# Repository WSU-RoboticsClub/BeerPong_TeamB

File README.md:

# BeerPong Team B

This repository contains the microcontroller and PC code for Team B's beer-pong playing robot.

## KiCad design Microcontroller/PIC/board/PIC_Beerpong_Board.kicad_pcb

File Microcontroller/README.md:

Microcontroller
===============

This Folder Contains the Microcontroller Code for the Robot

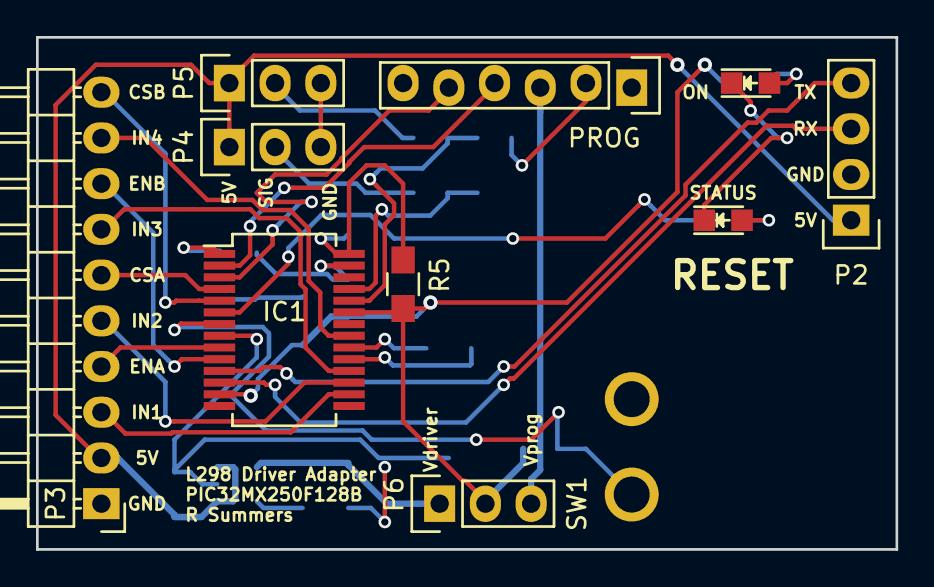
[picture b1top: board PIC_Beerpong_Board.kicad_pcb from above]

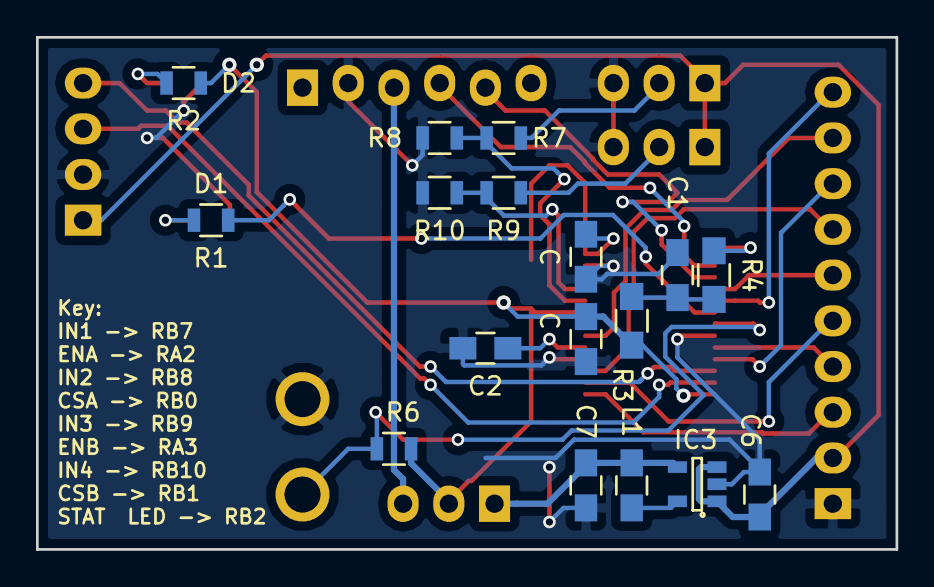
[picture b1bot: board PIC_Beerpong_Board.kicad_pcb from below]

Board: 2 copper layers, 47.8 x 28.4 mm, 28 parts (17 on the bottom side), 30 nets.

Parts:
C, C1, C2: C; C_0805_HandSoldering
C6: 4.7uF; C_0805_HandSoldering
C7: 10uF; C_0805_HandSoldering
C#2: C; C_0805_HandSoldering
D1, D2: LED; LED_0805
IC1: PIC32MX2xx/1xx; SSOP-28_5.3x10.2mm_Pitch0.65mm
IC3: LM3671; SOT-23-5
L1: 2.2uH; C_0805_HandSoldering
P2: CONN_01X04; Pin_Header_Straight_1x04
P3: CONN_01X10; Pin_Header_Angled_1x10
P4, P5, P6: CONN_01X03; Pin_Header_Straight_1x03
PROG: CONN_01X06; Pin_Header_Staggered_1x06
R1, R2, R6, R7, R8, R9, R10: R; R_0805
R3: 10k; R_0805_HandSoldering
R4: 470; R_0805_HandSoldering
R5: R; R_0805_HandSoldering
SW1: SW_PUSH; Switch

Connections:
+3V3: C.1, IC1.13, IC1.23, P6.2, R2.1, R3.1, R5.2, R6.1
+5V: C6.1, IC3.1, IC3.3, P2.1, P3.2, P4.1, P5.1
/3V3_PROG: P6.3, PROG.3
/HE1: P4.2, R9.1
/HE2: P5.2, R7.1
/Sheet56A51C6D/AVDD: C#2.1, IC1.28, R5.1
/Sheet56A51C6D/MRX: IC1.12, P2.3
/Sheet56A51C6D/MTX: IC1.11, P2.4
/Sheet56A51C6D/RA0: IC1.2, PROG.4
/Sheet56A51C6D/RA1: IC1.3, PROG.5
/Sheet56A51C6D/RA2: IC1.9, P3.4
/Sheet56A51C6D/RA3: IC1.10, P3.8
/Sheet56A51C6D/RB0: IC1.4, P3.6
/Sheet56A51C6D/RB1: IC1.5, P3.10
/Sheet56A51C6D/RB2: IC1.6, R1.1
/Sheet56A51C6D/RB3: IC1.7, R6.2, SW1.1
/Sheet56A51C6D/RB7: IC1.16, P3.3
/Sheet56A51C6D/RB8: IC1.17, P3.5
/Sheet56A51C6D/RB9: IC1.18, P3.7
/Sheet56A51C6D/RB10: IC1.21, P3.9
/Sheet56A51C6D/RB13: IC1.24, R7.2, R8.1
/Sheet56A51C6D/RB14: IC1.25, R9.2, R10.1
/Sheet56A51C6D/~MCLR: IC1.1, R4.1
/Sheet56A51CCD/Vout: C7.1, IC3.4, L1.2, P6.1
GND: C.2, C1.2, C2.2, C6.2, C7.2, C#2.2, D1.1, D2.1, IC1.8, IC1.19, IC1.27, IC3.2, P2.2, P3.1, P4.3, P5.3, PROG.2, R8.2, R10.2, SW1.2
unnamed: C1.1, R3.2, R4.2
unnamed: C2.1, IC1.20
unnamed: D1.2, R1.2
unnamed: D2.2, R2.2
unnamed: IC3.5, L1.1

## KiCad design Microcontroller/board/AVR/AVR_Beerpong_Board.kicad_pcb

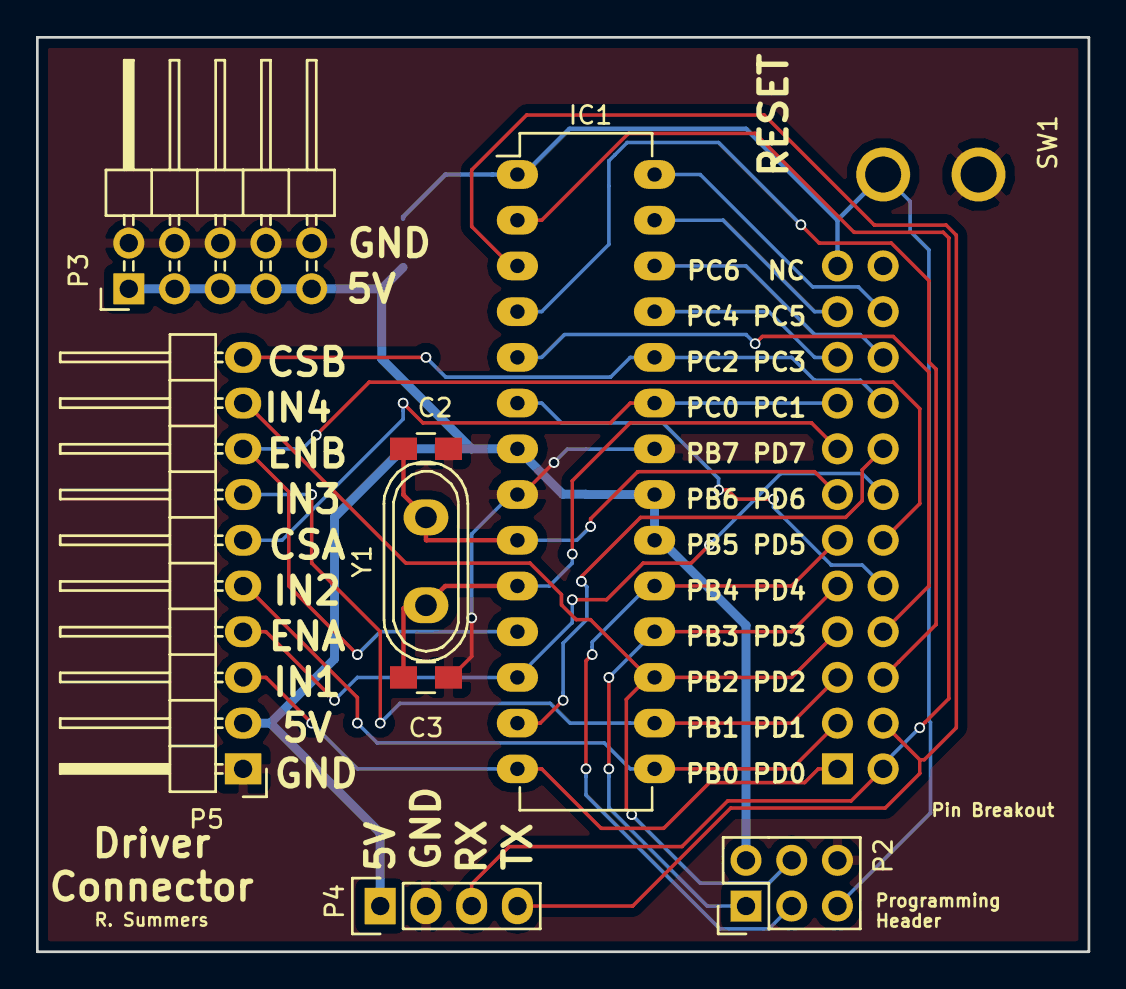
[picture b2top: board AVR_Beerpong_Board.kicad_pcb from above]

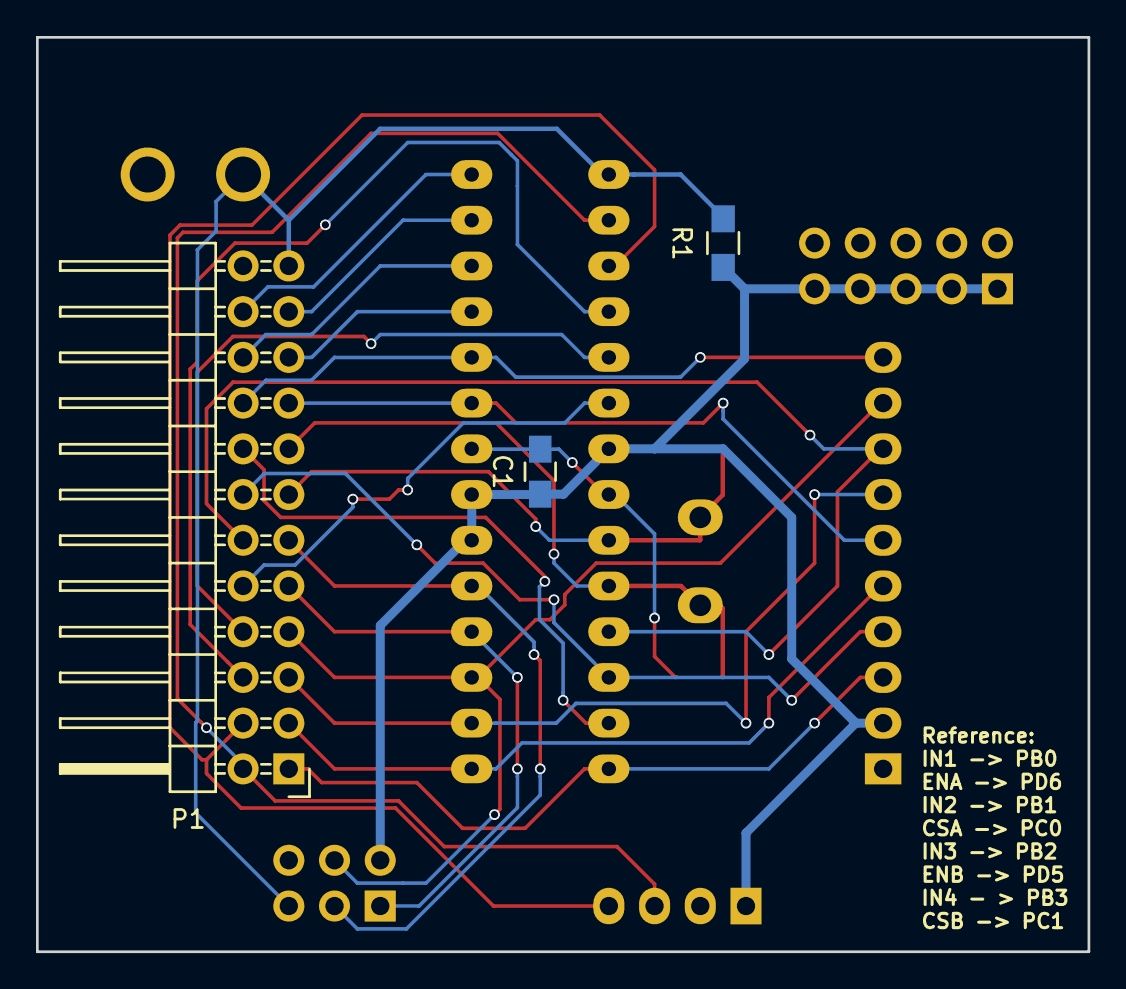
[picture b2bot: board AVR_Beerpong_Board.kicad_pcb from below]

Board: 2 copper layers, 58.4 x 50.8 mm, 12 parts (3 on the bottom side), 25 nets.

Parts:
C1: .1uF; C_0805_HandSoldering
C2, C3: 18pF; C_0805_HandSoldering
IC1: ATMEGA328P-P; DIP-28_W7.62mm_LongPads
P1: PIN_BREAKOUT; Pin_Header_Angled_2x12
P2: CONN_02X03; Pin_Header_Straight_2x03
P3: PWR; Pin_Header_Angled_2x05
P4: UART+PWR; Pin_Header_Straight_1x04
P5: Driver_Conn; Pin_Header_Angled_1x10
R1: 10k; R_0805_HandSoldering
SW1: SW_PUSH; Switch
Y1: 16MHz; Crystal_HC50-U_Vertical

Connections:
+5V: C1.1, IC1.7, IC1.20, IC1.21, P2.2, P3.1, P3.3, P3.5, P3.7, P3.9, P4.1, P5.2, R1.1
/CSA: IC1.23, P1.17, P5.6
/CSB: IC1.24, P1.18, P5.10
/ENA: IC1.12, P1.14, P5.4
/ENB: IC1.11, P1.12, P5.8
/PB0: IC1.14, P1.1, P5.3
/PB1: IC1.15, P1.3, P5.5
/PB2: IC1.16, P1.5, P5.7
/PB3: IC1.17, P1.7, P2.4, P5.9
/PB4: IC1.18, P1.9, P2.1
/PB5: IC1.19, P1.11, P2.3
/PB6: C2.2, IC1.9, P1.13, Y1.1
/PB7: C3.2, IC1.10, P1.15, Y1.2
/PC2: IC1.25, P1.19
/PC3: IC1.26, P1.20
/PC4: IC1.27, P1.21
/PC5: IC1.28, P1.22
/PC6: IC1.1, P1.23, P2.5, R1.2, SW1.1
/PD0: IC1.2, P1.2, P4.3
/PD1: IC1.3, P1.4, P4.4
/PD2: IC1.4, P1.6
/PD3: IC1.5, P1.8
/PD4: IC1.6, P1.10
/PD7: IC1.13, P1.16
GND: C1.2, C2.1, C3.1, IC1.8, IC1.22, P2.6, P3.2, P3.4, P3.6, P3.8, P3.10, P4.2, P5.1, SW1.2

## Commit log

2015-10-19 started microcontroller code
    added sublibinal library and started a mplabx project
2015-12-03 Added Flow for the Motors
2015-12-04 Motors will now run based on timer 1.
2015-12-04 Changed PWM frequency
2015-12-04 Updating definitions
2015-12-20 Refactor of the Microcontroller Code
    The new code changes establish an interface for a command module on a laptop
    to interface with the microcontroller to set and read RPMs of the motors
    so that a feedback system can be put in place.
    Future commits will add in computer-side GUI to read status of the Robot
2015-12-20 Bringing lib up to speed
2015-12-20 Addition of Qt Project Beginnings
    The Qt project will read from the Serial port to get status
    and set status of the robot
2015-12-20 Addition of GUI and Microcontroller Rework
    This commit adds in a GUI to control the microcontroller motor goals
    It also establishes efficient communication methods between the microcontroller and the computer.
2015-12-20 Changing color scheme
    This grays out the fields that can't be editted.
2015-12-21 Addition of makefile for linux compilation
    This commit adds in a makefile for linux compilation and upload.
    Once the makefile has been run, upload the hex file created onto the
    AVR microcontroller board.
2015-12-21 Addition of Feedback System
    This commit adds in feedback for motor 1 so that true RPMs can be known.
2015-12-21 Restructure of code to allow for AVR implementation
2015-12-21 Addition of PID controller
    This commit adds in a PID controller so that the motor can control its speed.
2016-01-06 Addition of Motor 2 controls
    Still buggy, figuring out sync issues.
2016-01-06 Cleanup of Repo and adjustment to GUI
    The GUI was corrected to ensure that commands were sent and received, and that sync would be fixed
    There are still issues with acquiring sync and keeping a stable line of communication. This should be reworked in the future.
    Also, it appears that the driver may be overcurrenting.
2016-01-06 Update of ignore file
2016-01-07 Addition of Board project files
    This commit adds in the breakout board project files for KiCAD
2016-01-18 Restructure of the GUI to utilize threading
    This also makes the code a LOT more stable. The PID controller calculations
    within an ISR were causing the microcontroller to periodicially crash, as the ISRs
    were taking too long to complete and were backing up. Instead, a flag is now set
    so that the background processing can occur without blocking interrupts.
2016-01-18 Cleaning up
2016-01-18 Addition of updated windows serial
    This commit adds in updated and corrected windows serial library
2016-01-22 Temporary commit
2016-01-22 Temporary commit 2
2016-01-22 Addition of extern def
2016-01-23 Addition of compiling code.
    This code is 100% untested on the microcontroller and drastically changes how the interface interracts with the controller.
2016-01-23 Restructure of the enumerations
2016-01-23 Addition of PID Control on computer side
    This commit changes the PID control to rely on the computer.
2016-01-23 Addition of PID Controller FPS
    Forgot to add in a timer for the controller.
2016-02-07 Refactor of the microcontroller code base
